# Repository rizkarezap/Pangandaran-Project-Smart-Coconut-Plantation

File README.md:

# Pangandaran Project: Smart Coconut Plantation
# Introduction

We see that some of our coconut farmers are having problems with their growing media. They cannot monitor the level of soil fertility in an exact manner so that they cannot provide proper care to the soil. From these problems we tried to make the device that we designed ergonomically. Farmers can use this tool easily and quick results with accuracy can be accounted for.

# The Device

We made this device using a microcontroller from the Arduino family, the Arduino Nano. We use analog pins to get data like
fertility,
pH
Light intensity,
soil moisture
simultaneously. The data is processed and displayed on a 64x64 LCD screen. Regarding the power source, we use a Lipo 3.7 V 800 mAh battery and add a charger module to recharge. We also added a Bluetooth communication module to send data from devices to smart devices, such as Android phones.

# The Tools

To make it easy to use, we recommend that you install the Arduino IDE. You can easily upload code using the device to the microcontroller that you are using.

# The Schematic

We make board designs that we have integrated with other devices. You can use Eagle CAD or KiCAD software to see the schematics we made.

# We Are Open To Discuss

We really hope to continue this product until we can distribute this device to a wider market. Therefore we expect your support. You can contact me through my email. All your support is very helpful for us.

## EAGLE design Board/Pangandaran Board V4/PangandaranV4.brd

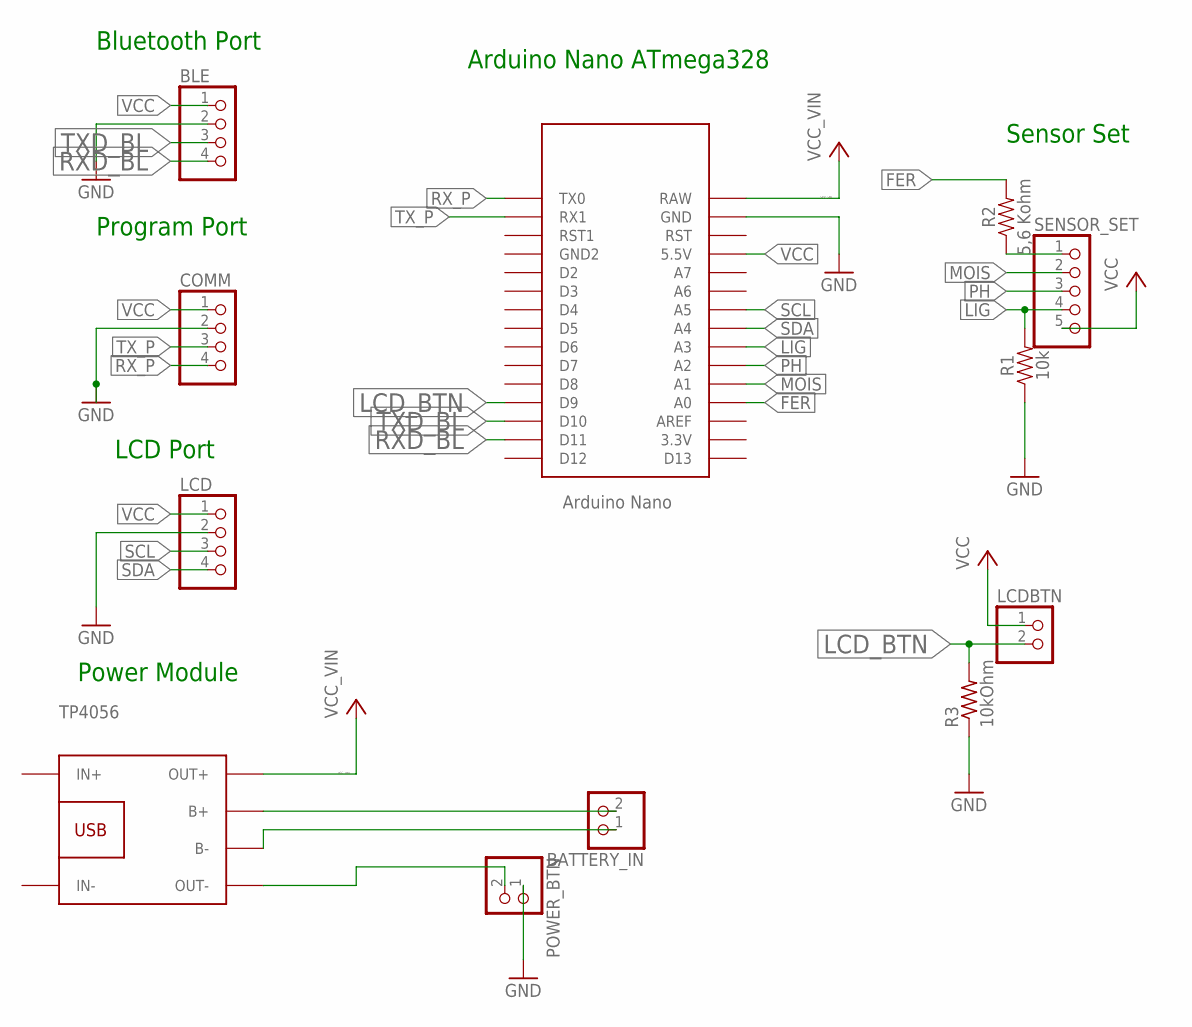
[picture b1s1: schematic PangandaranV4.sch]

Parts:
BATTERY_IN: PINHD-1X2; 1X02
BLE: PINHD-1X4; 1X04
COMM: PINHD-1X4; 1X04
LCD: PINHD-1X4; 1X04
LCDBTN: PINHD-1X2; 1X02
POWER_BTN: PINHD-1X2; 1X02
R1: 10k; 0603
R2: 5,6 Kohm; 0603
R3: 10kOhm; M1206
SENSOR_SET: PINHD-1X5; 1X05
TP4056: BATTERY-CHARGER-LI-PROT
U$2: NANO

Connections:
FER: R2.2, U$2.A0
GND: BLE.2, COMM.2, LCD.2, POWER_BTN.1, R1.1, R3.1, U$2.GND
LCD_BTN: LCDBTN.2, R3.2, U$2.D9
LIG: R1.2, SENSOR_SET.4, U$2.A3
MOIS: SENSOR_SET.2, U$2.A1
unnamed: R2.1, SENSOR_SET.1
unnamed: BATTERY_IN.2, TP4056.B+
unnamed: BATTERY_IN.1, TP4056.B-
unnamed: POWER_BTN.2, TP4056.OUT-
PH: SENSOR_SET.3, U$2.A2
RXD_BL: BLE.4, U$2.D11
RX_P: COMM.4, U$2.TX0
SCL: LCD.3, U$2.A5
SDA: LCD.4, U$2.A4
TXD_BL: BLE.3, U$2.D10
TX_P: COMM.3, U$2.RX1
VCC: BLE.1, COMM.1, LCD.1, LCDBTN.1, SENSOR_SET.5, U$2.5V (5.5V)
VCC_VIN: TP4056.OUT+, U$2.RAW

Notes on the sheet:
Power Module
Program Port
Arduino Nano ATmega328
LCD Port
Bluetooth Port
Sensor Set

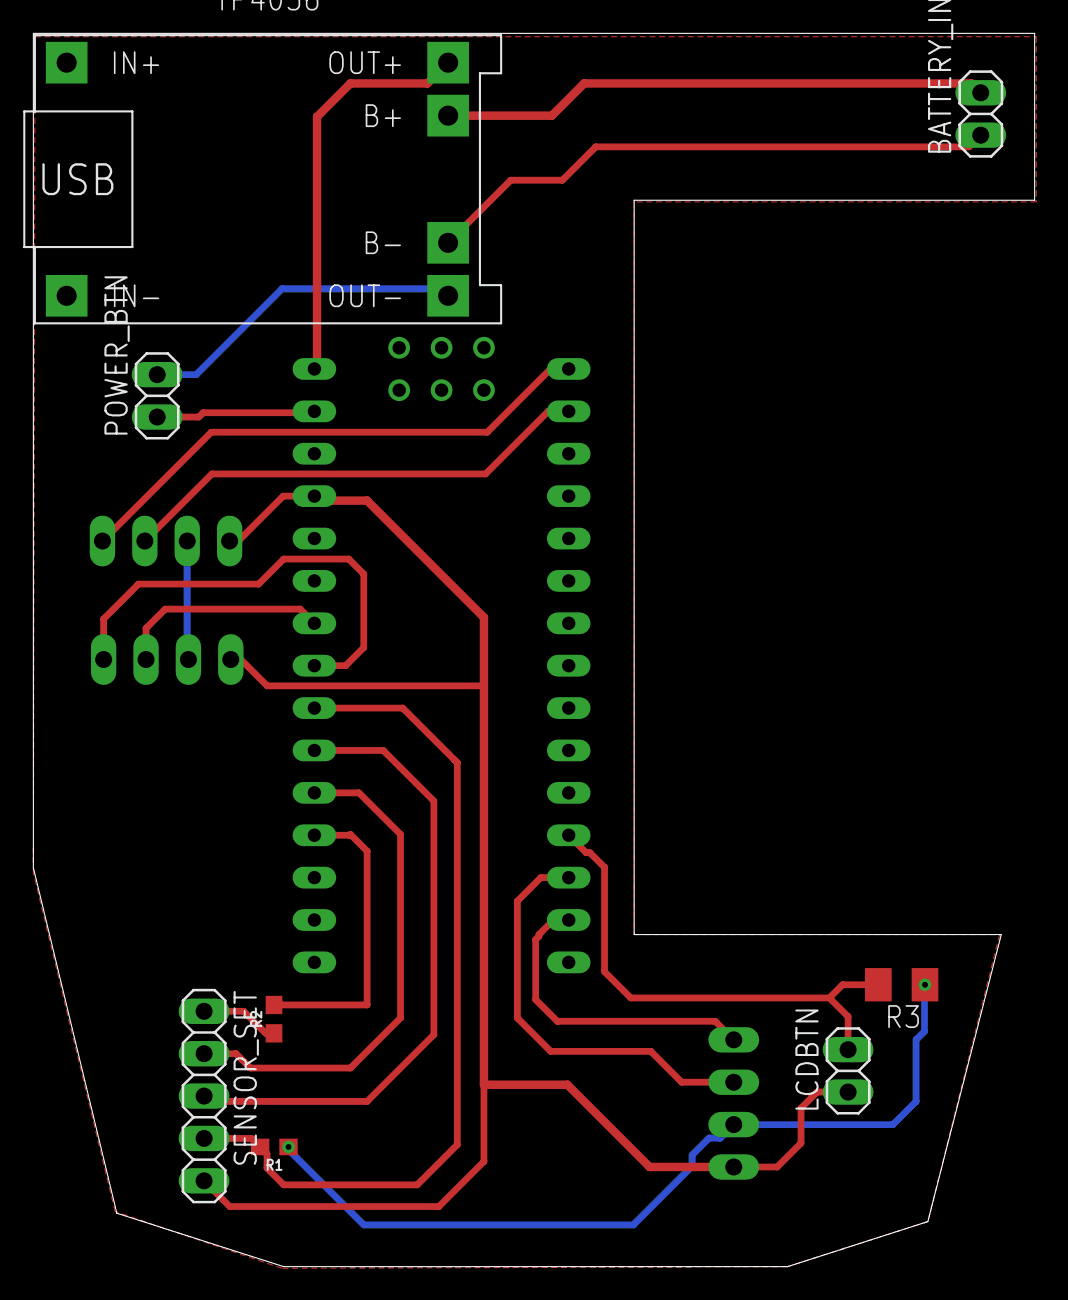
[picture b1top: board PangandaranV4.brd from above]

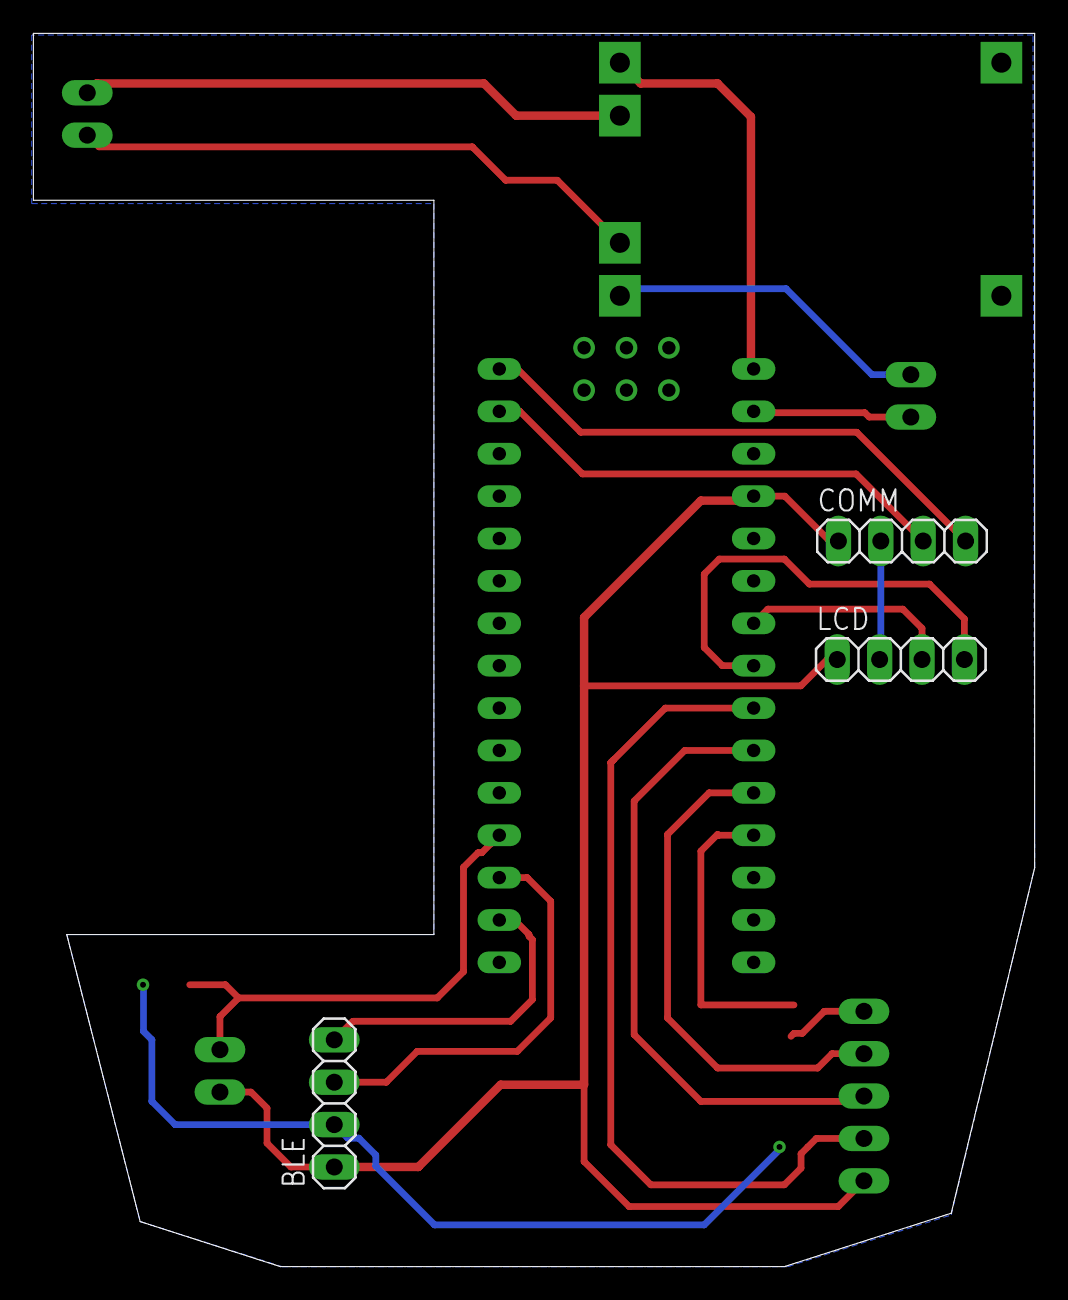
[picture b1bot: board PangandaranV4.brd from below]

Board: 2 copper layers, 60.0 x 73.9 mm, 12 parts (4 on the bottom side), 18 nets.

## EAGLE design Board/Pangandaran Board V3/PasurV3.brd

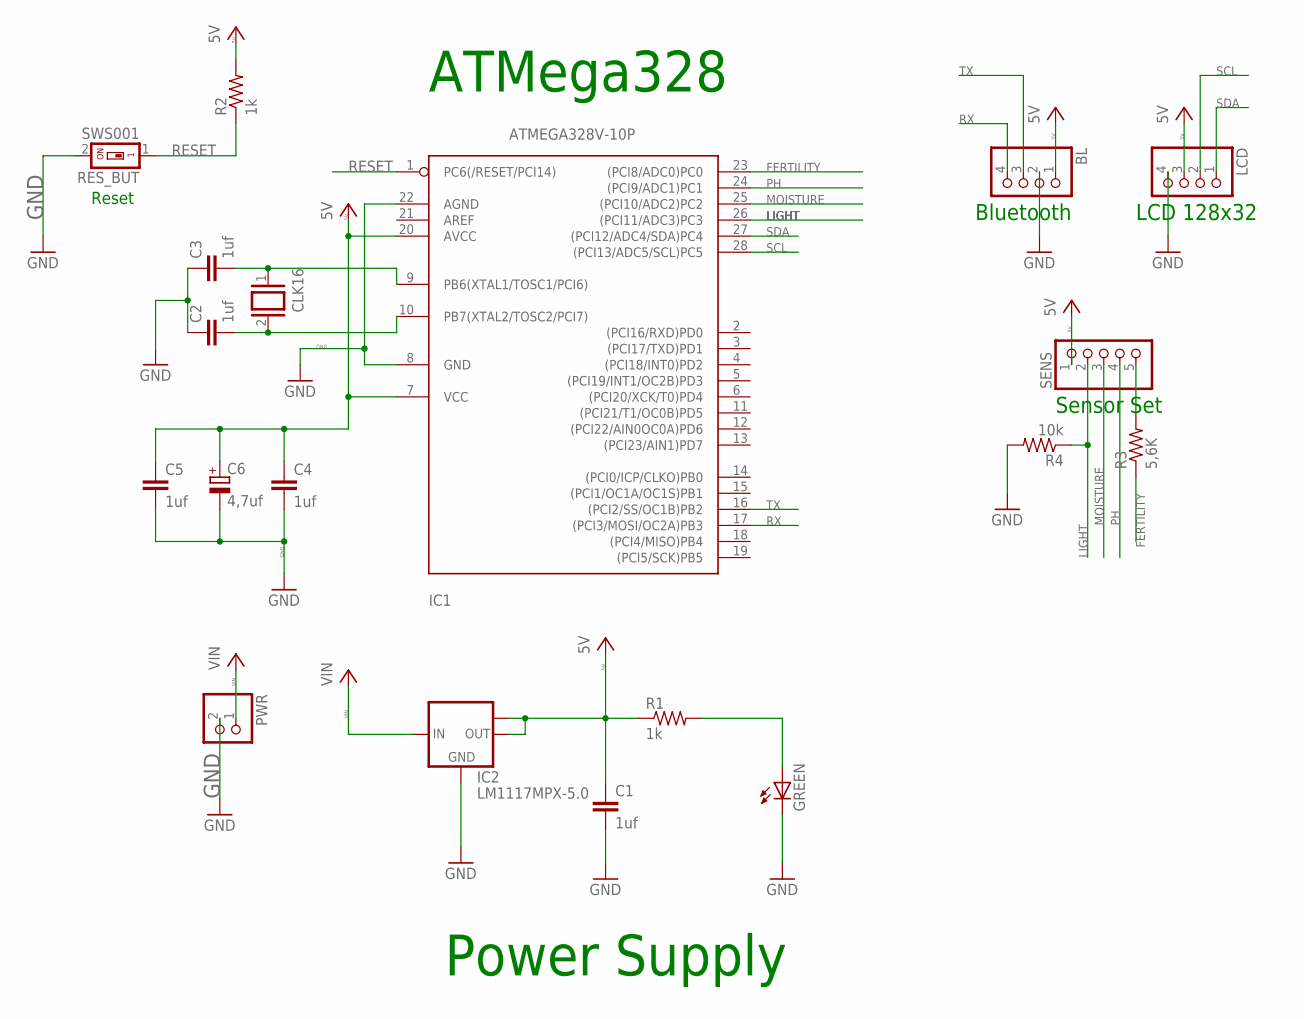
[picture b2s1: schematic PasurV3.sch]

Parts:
BL: PINHD-1X4; 1X04
C1, C2, C3, C4, C5: 1uf; C1206
C6: 4,7uf; A/3216-18W
CLK16: XTAL/S; QS
GREEN: LED_E; LED_1206
IC1: ATMEGA328V-10P; DIL28-3
IC2: LM1117MPX-5.0; SOT223
LCD: PINHD-1X4; 1X04
PWR: PINHD-1X2; 1X02
R1, R2: 1k; M1206
R3: 5,6K; M1206
R4: 10k; M1206
RES_BUT: SWS001; SMS-001
SENS: PINHD-1X5; 1X05

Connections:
5V: BL.1, C1.1, C4.1, C5.1, C6.+, IC1.7 (VCC), IC1.20 (AVCC), IC2.2 (OUT), IC2.TAB (OUT1), LCD.3, R1.1, R2.2, SENS.1
FERTILITY: IC1.23 ((PCI8/ADC0)PC0), R3.1
GND: BL.2, C1.2, C2.1, C3.1, C4.2, C5.2, C6.-, GREEN.C, IC1.8 (GND), IC1.22 (AGND), IC2.1 (GND), LCD.4, PWR.2, R4.2, RES_BUT.2
LIGHT: IC1.26 ((PCI11/ADC3)PC3), R4.1, SENS.2
MOISTURE: IC1.25 ((PCI10/ADC2)PC2), SENS.3
unnamed: C3.2, CLK16.1, IC1.9 (PB6(XTAL1/TOSC1/PCI6))
unnamed: C2.2, CLK16.2, IC1.10 (PB7(XTAL2/TOSC2/PCI7))
unnamed: GREEN.A, R1.2
unnamed: R3.2, SENS.5
PH: IC1.24 ((PCI9/ADC1)PC1), SENS.4
RESET: IC1.1 (PC6(/RESET/PCI14)), R2.1, RES_BUT.1
RX: BL.4, IC1.17 ((PCI3/MOSI/OC2A)PB3)
SCL: IC1.28 ((PCI13/ADC5/SCL)PC5), LCD.2
SDA: IC1.27 ((PCI12/ADC4/SDA)PC4), LCD.1
TX: BL.3, IC1.16 ((PCI2/SS/OC1B)PB2)
VIN: IC2.3 (IN), PWR.1

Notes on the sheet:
Power Supply
Reset
ATMega328
Bluetooth
LCD 128x32
Sensor Set

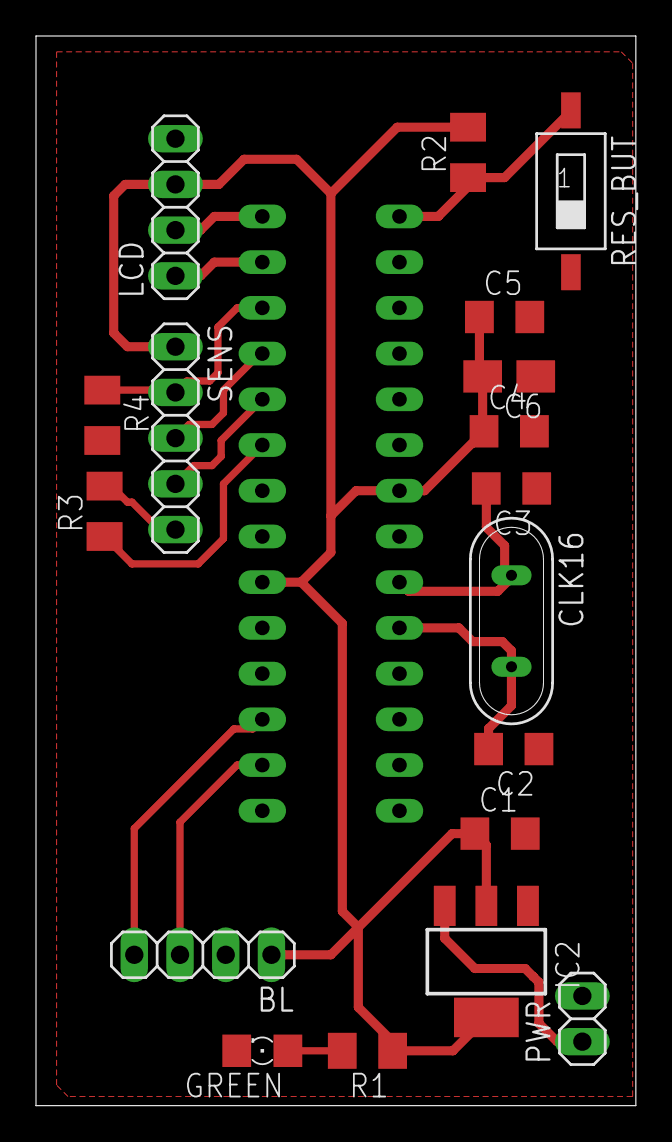
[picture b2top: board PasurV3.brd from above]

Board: 2 copper layers, 33.3 x 59.4 mm, 19 parts (1 on the bottom side), 16 nets.

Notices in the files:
parts and their libraries:
SparkFun-Resistors: Licensing: Creative Commons ShareAlike 4.0 International - https://creativecommons.org/licenses/by-sa/4.0
diy-modules: Released under the Creative Commons Attribution 4.0 International License: http://creativecommons.org/licenses/by/4.0
